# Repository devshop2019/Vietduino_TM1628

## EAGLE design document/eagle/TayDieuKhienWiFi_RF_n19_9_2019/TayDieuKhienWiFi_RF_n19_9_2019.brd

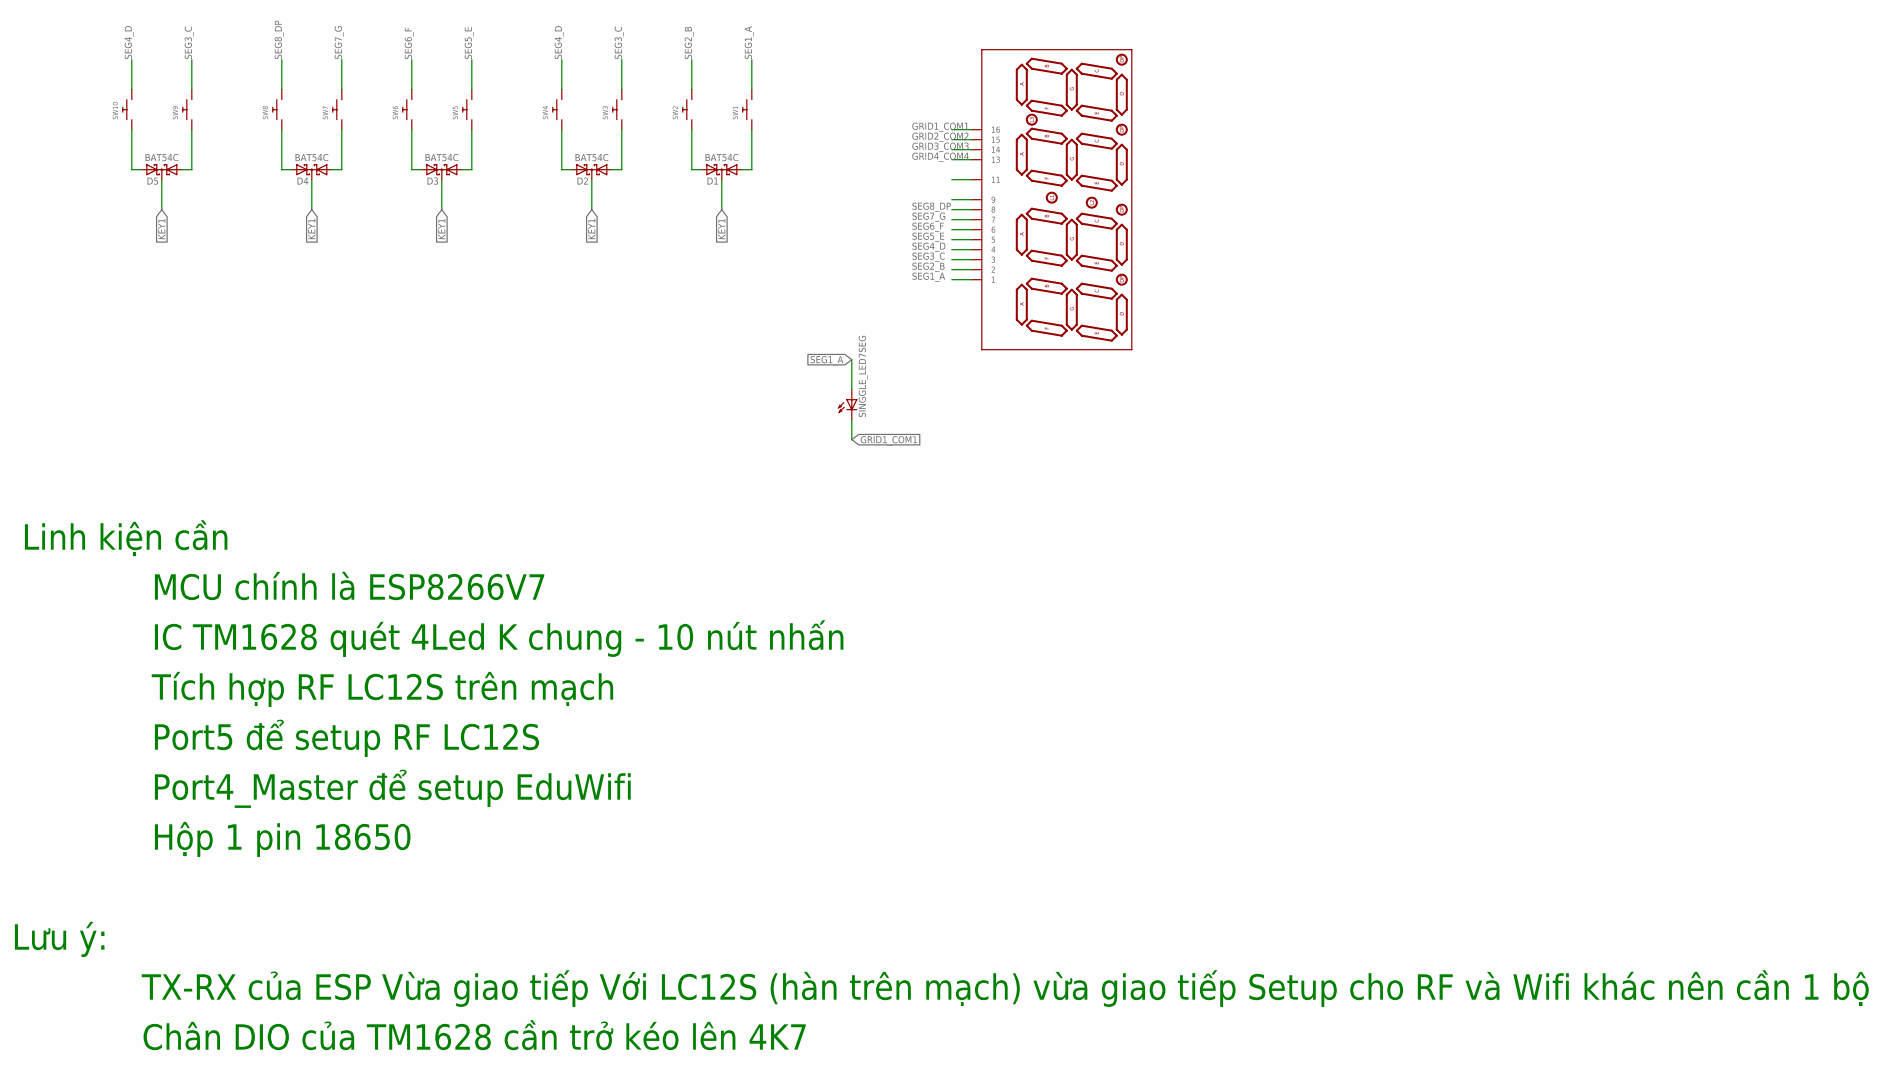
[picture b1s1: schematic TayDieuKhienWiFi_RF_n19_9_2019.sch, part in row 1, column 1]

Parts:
D1, D2, D3, D4, D5: BAT54C; SOT23
SINGGLE_LED7SEG: LEDCHIP-LED0603; CHIP-LED0603
SW1, SW2, SW3, SW4, SW5, SW6, SW7, SW8, SW9, SW10: SWITCH_PUSHBUTTONC&K_KSS; BTN_CK_KSS
U$1: 7-SEGMENT-4DIGIT; 7-SEGMENT-4DIGIT-YOUNGSUN

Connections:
GRID1_COM1: SINGGLE_LED7SEG.C, U$1.16
GRID2_COM2: U$1.15
GRID3_COM3: U$1.14
GRID4_COM4: U$1.13
KEY1: D1.3 (CC), D2.3 (CC), D3.3 (CC), D4.3 (CC), D5.3 (CC)
unnamed: D1.1 (A1), SW1.P$1
unnamed: D2.1 (A1), SW3.P$1
unnamed: D1.2 (A2), SW2.P$1
unnamed: D2.2 (A2), SW4.P$1
unnamed: D3.1 (A1), SW5.P$1
unnamed: D3.2 (A2), SW6.P$1
unnamed: D4.1 (A1), SW7.P$1
unnamed: D4.2 (A2), SW8.P$1
unnamed: D5.1 (A1), SW9.P$1
unnamed: D5.2 (A2), SW10.P$1
SEG1_A: SINGGLE_LED7SEG.A, SW1.P$2, U$1.1
SEG2_B: SW2.P$2, U$1.2
SEG3_C: SW3.P$2, SW9.P$2, U$1.3
SEG4_D: SW4.P$2, SW10.P$2, U$1.4
SEG5_E: SW5.P$2, U$1.5
SEG6_F: SW6.P$2, U$1.6
SEG7_G: SW7.P$2, U$1.7
SEG8_DP: SW8.P$2, U$1.8

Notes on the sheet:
Linh kiện cần
IC TM1628 quét 4Led K chung - 10 nút nhấn
Port5 để setup RF LC12S
Port4_Master để setup EduWifi
MCU chính là ESP8266V7
Tích hợp RF LC12S trên mạch
Hộp 1 pin 18650
Lưu ý:
TX-RX của ESP Vừa giao tiếp Với LC12S (hàn trên mạch) vừa giao tiếp Setup cho RF và Wifi khác nên cần 1 bộ đôi diod tách luồng Data như VietduinoUno
Chân DIO của TM1628 cần trở kéo lên 4K7

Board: 2 copper layers, 17 parts (0 on the bottom side), 20 nets, no tracks yet.

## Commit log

2019-09-19 Test Write 4 led, Read 20 Button With Node and Uno OK
2019-09-20 Add more Font led7seg, Wiring EagleCad

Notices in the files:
parts and their libraries:
SparkFun-Displays: Licensing: Creative Commons ShareAlike 4.0 International - https://creativecommons.org/licenses/by-sa/4.0
